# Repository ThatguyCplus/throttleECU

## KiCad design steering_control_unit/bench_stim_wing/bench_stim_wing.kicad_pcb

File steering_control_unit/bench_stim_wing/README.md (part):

# Bench stimulus FeatherWing

A FeatherWing for the EPS logger stack that does four jobs:

1. **Powers the whole stack from 12 V** (bench supply or the car battery), so the logger needs no USB power bank.
2. **Powers the Toyota steering-angle sensor** (12 V, ~30 mA, switched and fused) and passes its CAN on to the Feather M4 CAN.
3. **Drives the EPS signals** NEP (rpm) and VSP (speed) and, with the wheels off the ground, VT3/VT6 (fake driver torque).
4. **Switches IG1** for an EPS that's out of the car, on a bench.

It sits **between the Adalogger and the OLED FeatherWing**, on stacking headers, and every cable connector is right-angle and exits a board edge. The brief is [HANDOFF.md](HANDOFF.md).

> **Status: routed and checked in KiCad 10.0.8, nothing ordered.** The board is fully routed, and the Gerbers, BOM and CPL are in [fab/](fab/). Read [Before ordering](#before-ordering) first: several part numbers, the relay pinout and the JLC rotations still need a human check.
>
> | KiCad 10.0.8 check (with JLCPCB's rules, [bench_stim_wing.kicad_dru](bench_stim_wing.kicad_dru)) | Result |
> |---|---|
> | ERC | **0 errors**. 20 warnings: symbols drawn from KiCad 7's library differ from KiCad 10's copies, and KiCad 10 renamed `G6K-2` |
> | DRC | **0 copper errors, 0 unconnected, 0 schematic-parity issues**, including JLCPCB's 0.2 mm track-to-through-hole-pad rule and 1.0 mm / 0.15 mm text. Warnings left: stock footprint outlines touching their own pads (JLC clips those), footprints differ from KiCad 10's library copies, and J2's outline at the board edge (deliberate, edge connector) |

| Top (3D) | Back (3D) |
|---|---|
|  |  |

**Every part has a 3D model**, and the models ship with the project in [bench_stim_wing.3dshapes/](bench_stim_wing.3dshapes/). They're STEP files from KiCad's official library, referenced as `${KIPRJMOD}/bench_stim_wing.3dshapes/...`, so the 3D viewer and STEP export work on any machine with KiCad 7 to 10, whatever 3D libraries are installed. J1 shows the Feather stacking headers' female sockets (1×16 + 1×12). Only the test pads and the JP1 solder jumper have no model, because they're bare copper.

| Top layers | Back layers (seen from below) |
|---|---|
|  |  |

## Safety model

The user asked for this to be overbuilt. **Faking VT3/VT6 makes the EPS motor steer by itself**: front wheels off the ground (or the rack on a bench rig), hands clear of the wheel.

| Layer | What it does |
|---|---|
| **Relays, fail to the car** | Every EPS line (VT3, VT6, NEP, VSP) goes through an Omron G6K relay. The **NC** contact connects the EPS to the car's own wire, and the **NO** contact connects it to this board. No power, a reset, a crash or a blown fuse all leave the EPS wired exactly as the car wires it. |
| **ARM loop (hard kill)** | Both relay coils and the IG1 output are powered only through the **ARM loop on J5 pins 7–8**. Wire a normally-closed e-stop or a key switch there. **Loop open = car wiring, whatever the firmware does.** The red ARM LED shows the loop is closed. |
| **Enable bits** | Each output also needs its own bit from the TCA9534 I2C expander. The expander powers up with every pin as an input, and 100 kΩ pull-downs hold every driver off until firmware sets the bit. |
| **Clamped torque range** | The DAC uses its 2.048 V internal reference and the op-amp gain is 2.2, so the torque outputs top out at **4.5 V** even at full scale. They're also clamped to 0–5 V, with a 470 Ω series resistor each. |
| **Inject on the EPS side only** | NEP and VSP also feed the gauges, ECM, MCM, TCM and climate control. Only ever break them at the EPS with a breakout harness: the relay then isolates the EPS from the car wire, and the car side never sees the stimulus. |

**Latching DTCs.** The torque-sensor and sensor-supply codes (11/15/16/17/18/67) latch until erased with the SCS procedure, so a bad VT3/VT6 fake bricks assist until you clear them. The relay swaps only VT3/VT6: the real sensor stays connected to Vcc1/Vcc2 and stays powered, so the supply checks still see a real load.

**Plausibility rules** (from the manual, also in [EPS_PINOUT.md](../data_capture/EPS_PINOUT.md)):
- Never send speed without rpm. At ≥ 6.2 mph with ≤ 280 rpm for 3 s, the lamp comes on with DTC 22.
- Ramp speed changes, because VSS jumps also set DTC 22.
- Don't hold ≥ 2,000 rpm at ≤ 1 mph for more than 6 minutes.

**Key ON, engine off: the 12 V battery isn't being charged.** The DC-DC converter doesn't charge it in that state (LiBCM FAQ), so all assist current comes from the battery. Keep bench sessions short, or put a charger on the battery.

## Stack and mechanics

```
  OLED FeatherWing
  ─ female side of this wing's stacking headers ─
  BENCH STIM WING        top: relays, inductor, J2/J3/J4, LEDs   (tallest part: relays, 5.2 mm)
                         back: logic, test pads, J5              (back parts <= 1.25 mm, J5 4.25 mm)
  ─ long male tails into the Adalogger's female headers ─
  Adalogger FeatherWing  (CR1220 holder and microSD socket on its top: ~2-4 mm)
  Feather M4 CAN         (USB-C at the left end, CAN terminal block at the right end)
  EPS tap wing           (bottom wing, connectors facing down)
```

Why this slot:
- **Feather ↔ Adalogger was ruled out.** The Feather M4 CAN's 3.5 mm CAN terminal block (right end) and USB-C (left end) sit right where this board's back and its edge connectors would be.
- **The Adalogger's top is low.** The tallest parts there are the CR1220 holder (x ≈ 3–17 mm) and the microSD socket (x ≈ 27–40 mm). That's why every back-side part on this wing is ≤ 1.25 mm tall, and J5 sits at the right end, where the Adalogger is bare.
- **The OLED's underside is bare,** so the relays (5.2 mm), the inductor (3 mm) and the 4.25 mm GH connectors fit under it, inside the ~8.5 mm stacking-header gap.

Use **Feather stacking headers** (female on top, long male tails) on this wing. **Check the gap with the real parts before soldering the headers.**

### Grounding, and running with the logger

This wing and the [EPS tap wing](../data_capture/hardware/eps_tap_wing/README.md) logger run **alone or together, in the car or on a bench EPS**. [STACK_MODES.md](../data_capture/STACK_MODES.md) covers every combination: power, ground, which pins to wire, and the timers and I2C addresses they share.

**The one rule:** J2's ground (the stack's ground) goes to the **ECU end of A4 (PG, BLK)**, spliced within ~10 cm of the EPS connector. On a bench, it goes to the EPS's A4 terminal. It must not go to a chassis bolt or the battery. A4 carries the 40 A motor return, so anywhere else puts an offset between the stack and the EPS's sensor ground (B9).
- **Logger accuracy:** that offset would shift every logger reading.
- **Faked torque:** it would also shift the VT3/VT6 values this board produces.

**Leave J4.3 and J5.4 (GND) unwired in the car,** so there's only one ground path. Fitted but unpowered (J2 unplugged), this board is passive: the relays rest on the car's wiring, and the logger keeps floating on its power bank.

### Feather specification check

| Spec item | This wing |
|---|---|
| 0.9" × 2.0", 0.1" holes at each corner | 22.86 × 50.8 mm, four 2.5 mm holes 2.54 mm in from the edges |
| 16-pin and 12-pin header positions | Same footprint as the EPS tap wing; `make_pcb.py` asserts the pad positions every build |
| Power: take 3.3 V from the Feather | The expander and DAC run on the Feather's 3V3 (about 1 mA) |
| Powering the Feather from a wing | 5 V goes into the **USB pin through a Schottky** (D6). On the Feather M4 CAN the USB pin is VBUS straight off the USB-C connector, and the Feather's own MBR540 then feeds its regulator, so this is the normal path (checked against Adafruit's schematic) |
| Avoid AREF, RX/TX, SPI and its CS | AREF, RX and SPI are untouched. **TX is used** (VSP output): only D4 and RX/TX are left free in this stack, and NEP and VSP each need their own timer |
| I2C pull-ups on Wings | Not fitted: the Adalogger already has them |

### USB and 12 V at the same time

- **Our side:** the buck makes 5.05 V. After D6's drop the Feather's USB pin sees about **4.7 V**.
- **With a PC plugged in:** the PC's 5 V is higher, so the PC carries the stack and D6 stays off. This board never back-feeds the PC.
- **With 12 V gone:** D6 also stops the USB cable from powering this board's 5 V rail. The relays and op-amp go dead, and so the EPS is on the car wiring.

**A LiPo on the Feather.** If one is plugged into the Feather's JST, its charger draws up to ~200 mA from this 5 V rail. The buck is rated 0.6 A, so that still fits, but leave the LiPo off unless you want it charging.

**The current clamp's supply.** The HSTS016L on the tap wing takes its 5 V from the USB pin, so on 12 V alone it gets ~4.7 V. Its output is read as Vout − Vref, which cancels most of that offset, but **check its zero at key-on** the first time.

## Connectors

All connectors are right-angle and exit a board edge. **JLC assembles the three GH connectors** (J3, J4, J5: SMD, 1.25 mm pitch, awkward by hand). J2 (through-hole PH) and the Feather stacking headers are hand-soldered. The GH parts have locking latches: use JST GH housings (GHR-0xV-S) with SSHL-002T-P0.2 contacts, or buy pre-crimped GH leads.

**J2, 12 V IN** (top edge, JST PH S2B-PH-K, 2 mm). Pin 1 (marked +) is +12 V and pin 2 is GND. 2 A fuse.

**J3, SAS / CAN** (left end, JST GH 6-way). This is a pass-through: build one cable to the SAS, plus one pair from pins 5/6 to the Feather's CAN terminal.

| Pin | Net | Goes to |
|---|---|---|
| 1 | SAS 12V | SAS power (switched, 0.1 A PTC) |
| 2 | GND | SAS ground |
| 3 | CANH | SAS CAN-H |
| 4 | CANL | SAS CAN-L |
| 5 | CANH | Feather M4 CAN terminal **pin 3 (H)** |
| 6 | CANL | Feather M4 CAN terminal **pin 1 (L)** |

The Feather's terminal has a 120 Ω terminator behind a solder jumper (SJ2). The SAS bus here is two nodes, so close SJ2 unless the SAS end already terminates the bus.

**Second microcontroller:** J3 is also the stack's port for another board. Splice its CAN-H/CAN-L into the pin 5/6 lead (no ground or power wire), keep exactly two terminators on the bus (about 60 Ω across H/L, powered off), and use IDs 0x6C0–0x6CF. See [AUX_LINK.md](../data_capture/AUX_LINK.md).

**J4, TORQUE** (right end, top, JST GH 5-way). Break the torque sensor's VT3 and VT6 wires in a breakout harness: the CAR side goes to the sensor, the EPS side to the EPS.

| Pin | Net |
|---|---|
| 1 | VT3 EPS side (gearbox 7-pin 3 / ECU B10) |
| 2 | VT3 sensor side |
| 3 | GND (leave unwired in the car: the reference comes through J2's ground, see below) |
| 4 | VT6 EPS side (gearbox 7-pin 1 / ECU B8) |
| 5 | VT6 sensor side |

**J5, ECM / IG1 / ARM** (right end, back, JST GH 8-way). The back silk marks "J5" with pins "1" and "8"; the pin names are below.

| Pin | Net | Notes |
|---|---|---|
| 1 | IG1 OUT | Switched 12 V, 0.5 A PTC. Bench EPS only (ECU B6) |
| 2 | NEP CAR | Car-side NEP wire (ECM) |
| 3 | NEP EPS | EPS B14 |
| 4 | GND | Separates the 12 V-level pins from the 5 V-level pins. Leave unwired in the car |
| 5 | VSP EPS | EPS B4 |
| 6 | VSP CAR | Car-side VSP wire (VSS) |
| 7 | ARM+ | 5 V out to the ARM loop (0.1 A PTC) |
| 8 | ARM | Back from the loop: powers the relay coils, enables IG1 |

**Loopback for free.** The tap wing's J2 reads NEP (D6), VSP (D5), VT3 (A2) and VT6 (A3). Tap the **EPS side** of the breakout harness and the logger records exactly what the EPS receives, including whether the relay switched.

## Circuit summary

| Block | Parts | Notes |
|---|---|---|
| 12 V input | F1 2 A fast fuse → D1 SS34 (reverse polarity) → D2 SMBJ24CA TVS → C1 10 µF/50 V | Everything on +12 V is rated ≥ 40 V; the TVS clamps a load dump to ~39 V |
| 5 V | U1 LMR16006 (40 V, 65 V transient, 0.6 A, 0.7 MHz), L1 22 µH, D4 catch diode, 56k/10k → 5.05 V | ~250 mA load: stack ~150 mA, relays 2 × 28 mA, LEDs |
| Feather feed | D6 PMEG6010 → Feather USB pin | See [USB and 12 V at the same time](#usb-and-12-v-at-the-same-time) |
| SAS power | Q1 Si2319 high side, Q2 2N7002, F2 0.1 A PTC | Expander P0. **JP1** (open as shipped): bridge for "SAS always on", for use with the unmodified logger firmware |
| IG1 out | Q3 Si2319, Q4 + Q5 in series (IG1_EN **and** ARM), F4 0.5 A PTC | Expander P1 |
| Relays | K1 (VT3/VT6), K2 (NEP/VSP): G6K-2F-Y 5 V, Q6/Q7 drivers, 1N4148WS flyback | Expander P2, P3. Coils fed from ARM |
| NEP | D4 (PA14) → Q8 → open drain, **4.7 kΩ to 12 V**, 100 Ω series | Like the ECM's open-collector output |
| VSP | TX (PB16) → Q9 → open drain, **4.7 kΩ to 5 V**, 100 Ω series | Like the VSS |
| Torque | U2 MCP4728 (I2C 0x60, 2.048 V ref, gain ×1) → U3 MCP6004 on 5 V, gain 2.2 → 470 Ω → BAT54S clamp | DAC A = VT3, B = VT6. DAC C and D go **straight** to test pads 10/11 as spare 0–2.048 V outputs (unbuffered, ~mA); op-amp sections C/D are parked as grounded followers |
| Expander | U4 TCA9534 (I2C **0x20**) | P0 SAS, P1 IG1, P2 K1, P3 K2 (outputs); P4 ARM sense, P5 12 V sense (inputs); P6/P7 on test pads |

**Pulse output polarity.** GPIO high pulls the output low (open drain), and the idle level is high. Both D4 and TX sit on independent timers: PA14 on TCC1/WO2 or TCC2/WO0, PB16 on TC6/WO0 or TCC0/WO4. **Don't use TC3**: the logger (`eps_logger`) uses it for its 1 kHz sample tick. The rates are low (NEP 1.5 pulses/rev: 22.5 Hz at 900 rpm; VSP ~1.24 Hz per mph, **unverified**), so plain `micros()` timing also works.

**I2C addresses** on the shared bus: RTC 0x68, OLED 0x3C, ADS1115 0x48, **MCP4728 0x60, TCA9534 0x20**. There are no clashes.

### LEDs

Top side, in one row above the relays. Left to right: **5V, SAS, IG1, ARM, TQ, SIG, NEP, VSP**; the legend is also on the back silk. The 12 V LED is in the top-left corner. TQ and SIG light when their relay is energised. NEP and VSP blink with the pulse outputs.

### Test pads (back)

The pads are numbered 1–15 on the back silk; names don't fit at JLC's 1 mm minimum text height.

| TP | Net | TP | Net | TP | Net |
|---|---|---|---|---|---|
| 1 | GND | 6 | NEP out | 11 | DAC D (raw, 0–2.048 V) |
| 2 | +12 V | 7 | VSP out | 12 | ARM |
| 3 | +5 V | 8 | VT3 out | 13 | Expander P6 |
| 4 | +3V3 | 9 | VT6 out | 14 | Expander P7 |
| 5 | USB pin | 10 | DAC C (raw, 0–2.048 V) | 15 | GND |

## Design rules

| Item | Value |
|---|---|
| Layers | 4: **F.Cu** parts + signals + GND pour, **In1.Cu** solid GND, **In2.Cu** signals + GND pour, **B.Cu** parts + signals + GND pour |
| Signal tracks | 0.15 mm (mA and below) |
| Power tracks | +12 V path and IG1 0.5 mm; +5 V, USB, buck SW, SAS and ARM 0.4 mm; 3V3 0.3 mm |
| Clearance | 0.127 mm; **0.21 mm from tracks to plated through-hole pads** (JLCPCB's 0.2 mm pad-to-trace rule) |
| GND plane | In1 is a solid GND pour; a few low-speed signals cross it where routing needed the room |
| Silkscreen | All text >= 1.0 mm high with a 0.15 mm stroke (JLCPCB minimum) |
| JLCPCB rules | [bench_stim_wing.kicad_dru](bench_stim_wing.kicad_dru), the 4-layer 1 oz set from [Cimos/kicad-druid](https://github.com/Cimos/kicad-druid) (MIT). KiCad loads it as the project's custom rules |
| Vias | 0.45/0.2 mm signal, 0.6/0.3 mm power |
| Assembly | **Both sides** (SMD top and back). The back carries only parts ≤ 1.25 mm tall |

## Files

| File | What it is |
|---|---|
| [bench_stim_wing.kicad_sch](bench_stim_wing.kicad_sch) / [schematic PDF](doc/bench_stim_wing_schematic.pdf) | Schematic (generated) |
| [bench_stim_wing.kicad_pcb](bench_stim_wing.kicad_pcb) | Board, 50.8 × 22.86 mm (FeatherWing), 4 layers |
| [doc/](doc/) | 3D renders (KiCad 10) and layer renders of the top and back |
| [bench_stim_wing.3dshapes/](bench_stim_wing.3dshapes/) | The 3D models every footprint points to (KiCad library STEP files, CC-BY-SA 4.0 with the KiCad library exception) |
| [fab/](fab/) | Gerbers + drill (zipped), JLC BOM and CPL. All SMD parts including the GH connectors; J1 (stacking headers), J2, JP1 and the test pads are excluded |
| [gen/](gen/) | Generators. Everything comes from [gen/design.py](gen/design.py) (parts and nets) and [gen/placement.py](gen/placement.py) (positions, silk, hand stubs). [gen/bench_stim_wing.ses](gen/bench_stim_wing.ses) is the accepted Freerouting result |

## Rebuilding

The board was generated in a Linux cloud session. The generators ran on **KiCad 7.0.11**, the version Ubuntu ships. Sign-off ran on **KiCad 10.0.8**, which [gen/setup_kicad10.sh](gen/setup_kicad10.sh) installs from the official `kicad/kicad` Docker image. That image comes through Google's Docker Hub mirror, because KiCad's Launchpad PPA is blocked there and Docker Hub rate-limits anonymous pulls. The script runs KiCad 10 through `chroot`, which needs root. Routing used **Freerouting 1.9.0** on Java 21, under `xvfb-run`. The files are written in KiCad 7's format. KiCad 10 opens them and asks to upgrade on save. Upgrading is fine, but then the generators would overwrite your edits, so pick one way of working.

```bash
cd gen
sh route.sh --keep-routing   # rebuild everything from the committed routing (bench_stim_wing.ses)
sh route.sh                  # full re-route with Freerouting (a different result every run)
```

`route.sh` expects `kicad-cli` and a Python that can `import pcbnew` (`PY=...`). A full re-route also needs the Freerouting 1.9 jar (`JAR=...`). On Windows with KiCad 10, point `PY` at KiCad's bundled `python.exe`, and set `KICAD_SYMBOL_DIR` / `KICAD_FOOTPRINT_DIR` if the libraries aren't found.

**How it got to 0 unconnected (and JLCPCB-clean):**
- **Freerouting version.** 2.0.1 ignored its pass limit and never finished, so routing uses 1.9.0 with `-oit 100`. Without that flag the post-route optimiser runs for hours.
- **Rules.** Signal tracks are 0.15 mm with 0.127 mm clearance, but tracks stay **0.21 mm from plated through-hole pads**, per JLCPCB's 0.2 mm pad-to-trace rule. KiCad 7 doesn't export per-pad clearances to Freerouting, so `make_pcb.py` grows the through-hole pads in the router's copy of the board instead (`dsn_router_tweaks`).
- **Spare DAC channels simplified.** DAC C/D used to have their own op-amp stages. Routing those with the wider through-hole clearance left nets unroutable, so they now go straight to test pads 10/11.
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
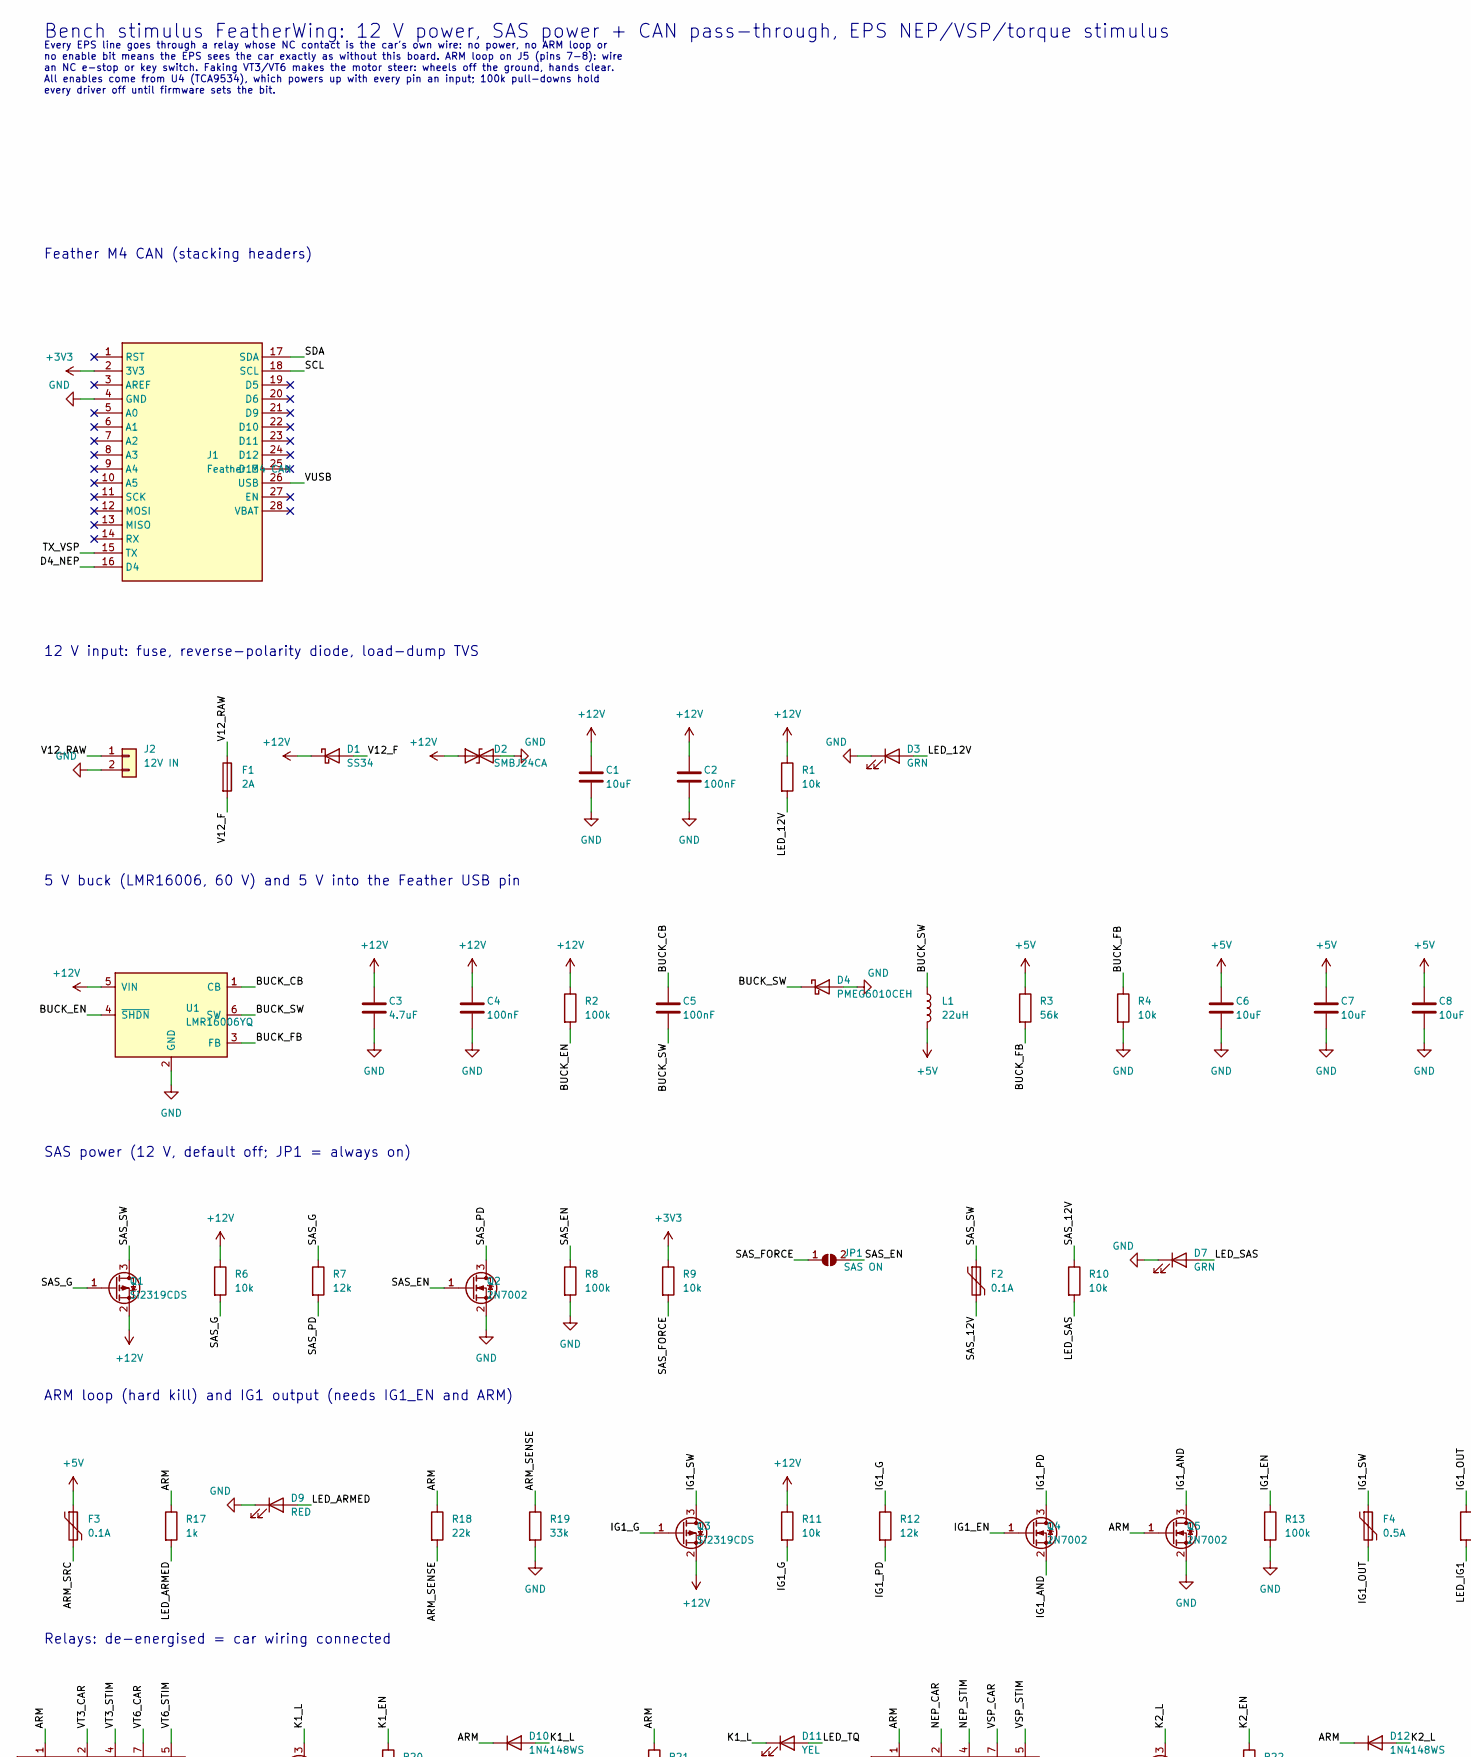
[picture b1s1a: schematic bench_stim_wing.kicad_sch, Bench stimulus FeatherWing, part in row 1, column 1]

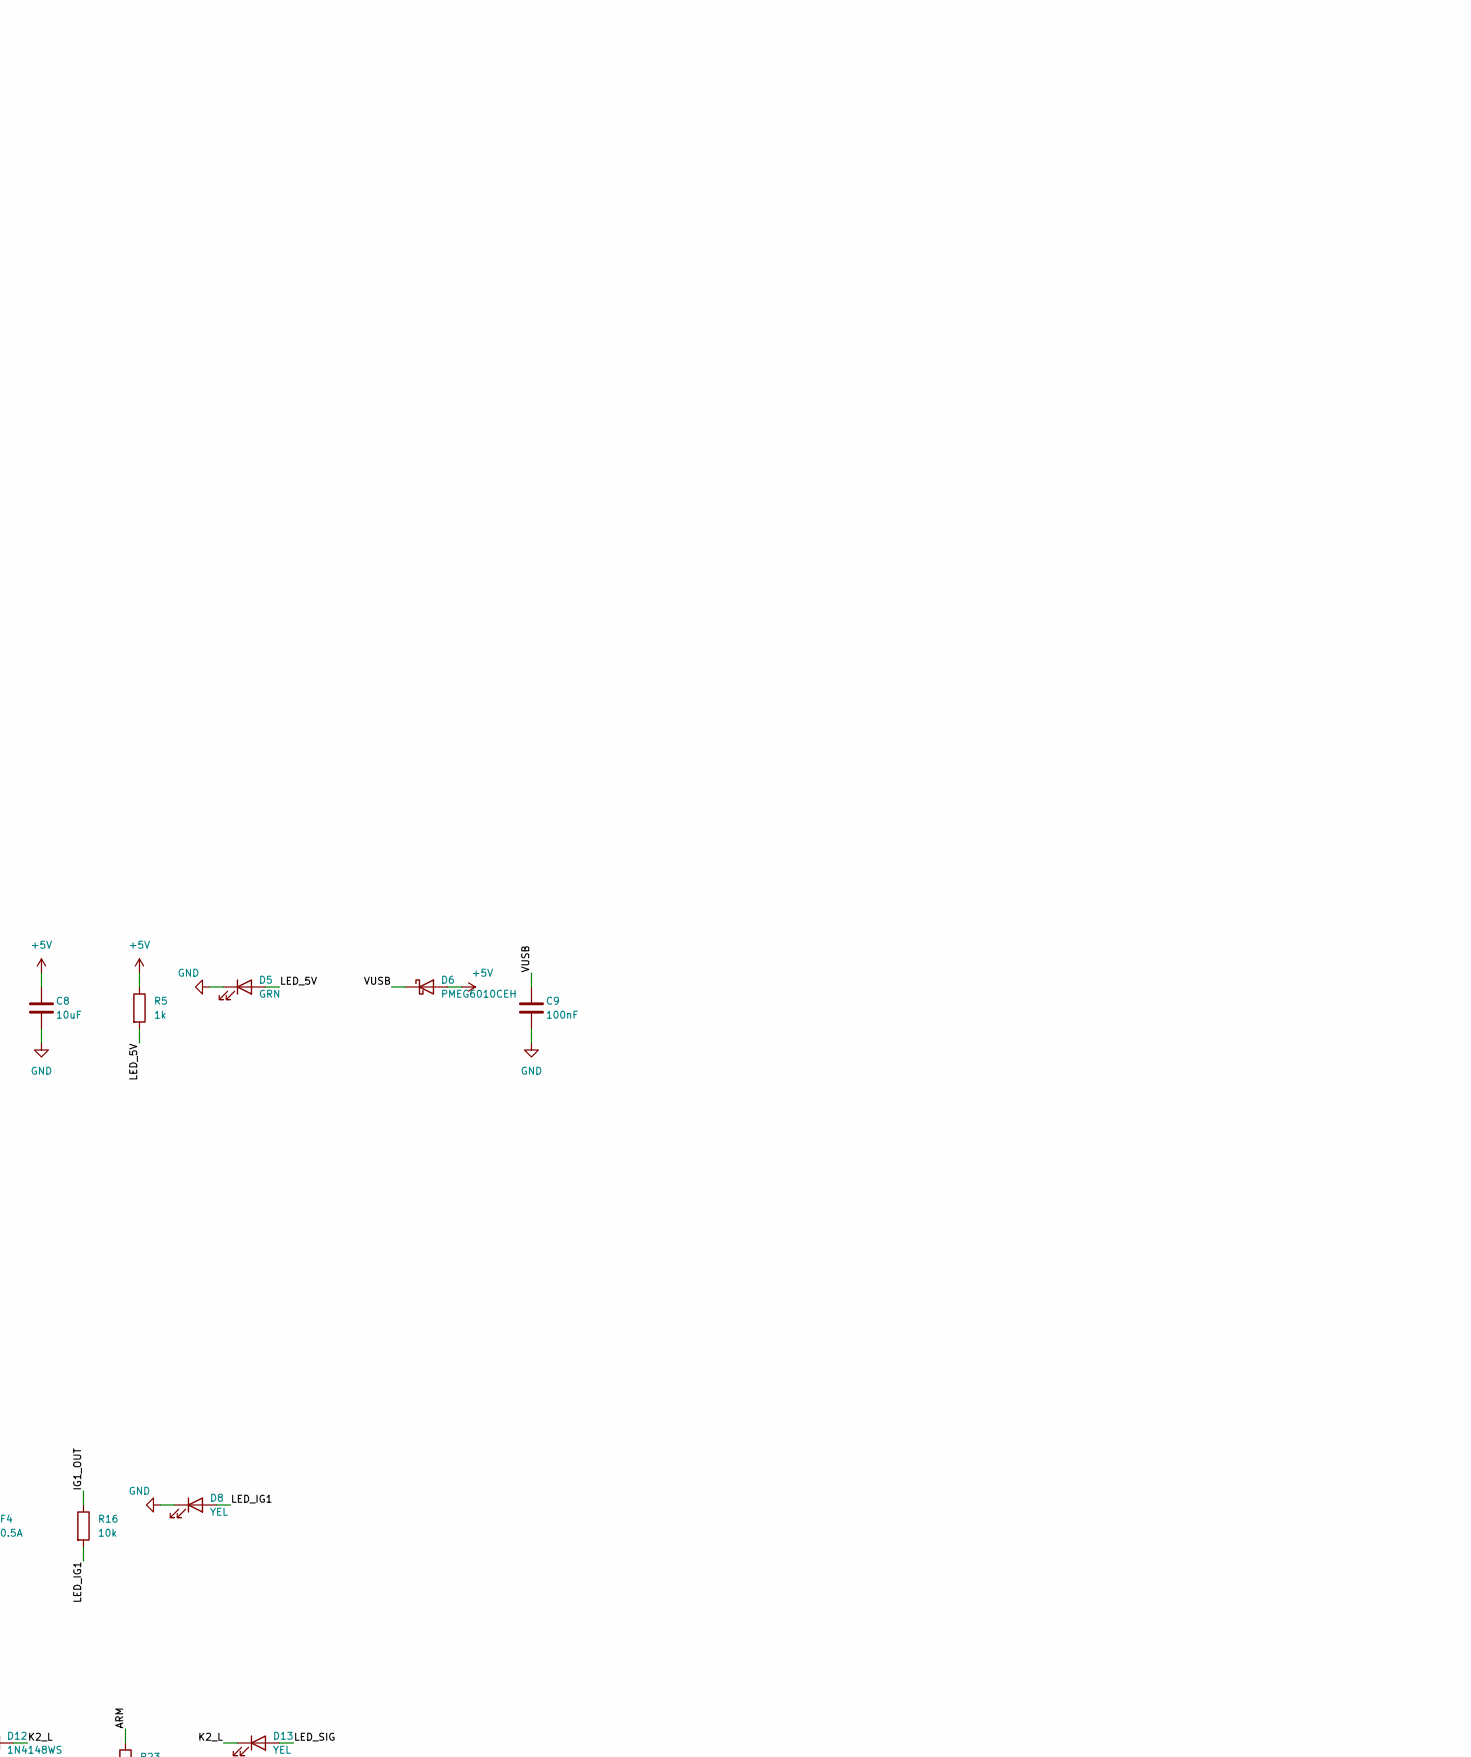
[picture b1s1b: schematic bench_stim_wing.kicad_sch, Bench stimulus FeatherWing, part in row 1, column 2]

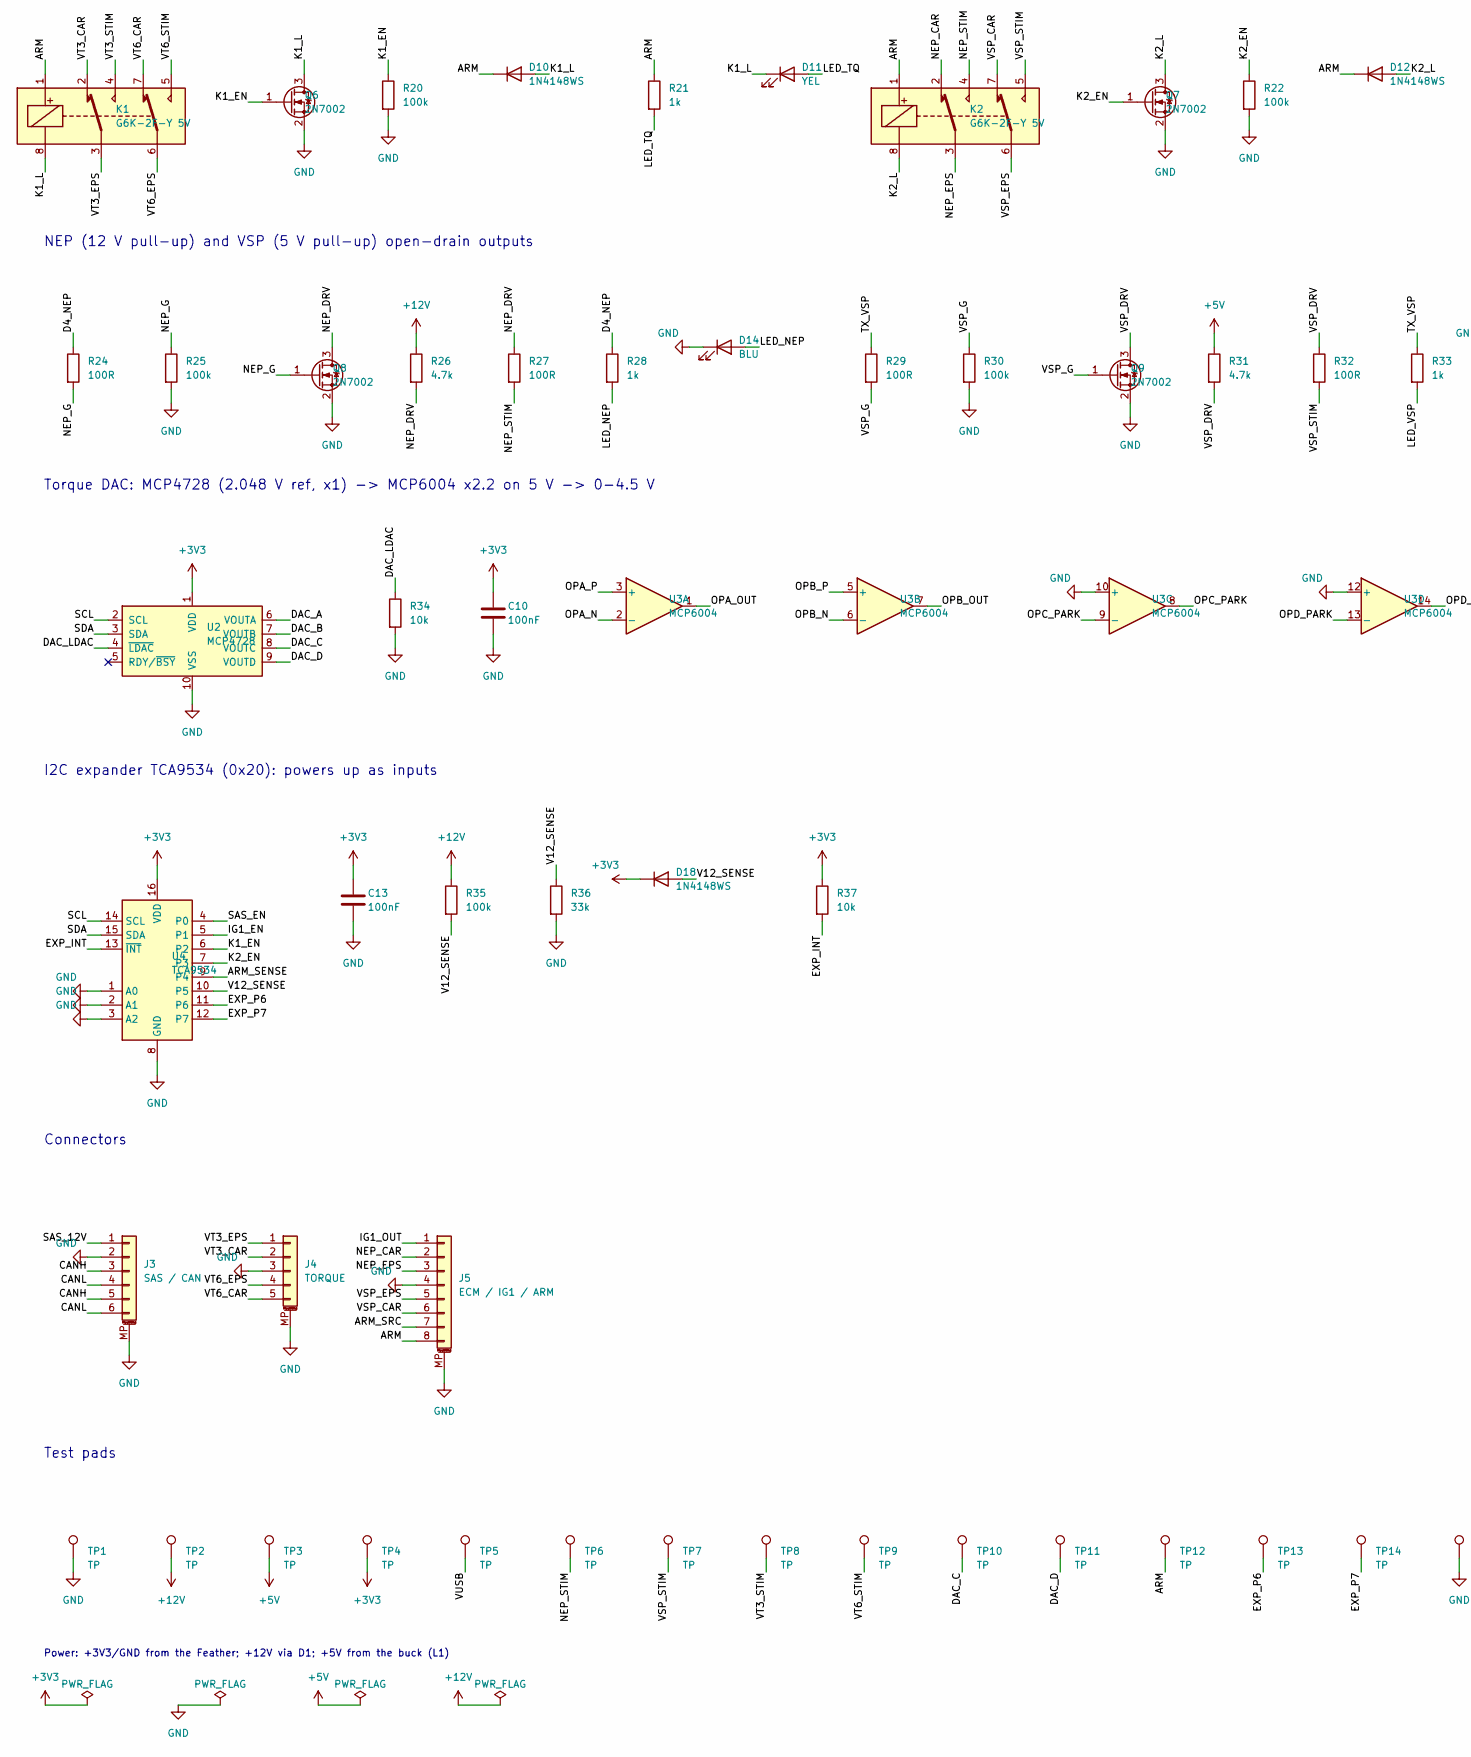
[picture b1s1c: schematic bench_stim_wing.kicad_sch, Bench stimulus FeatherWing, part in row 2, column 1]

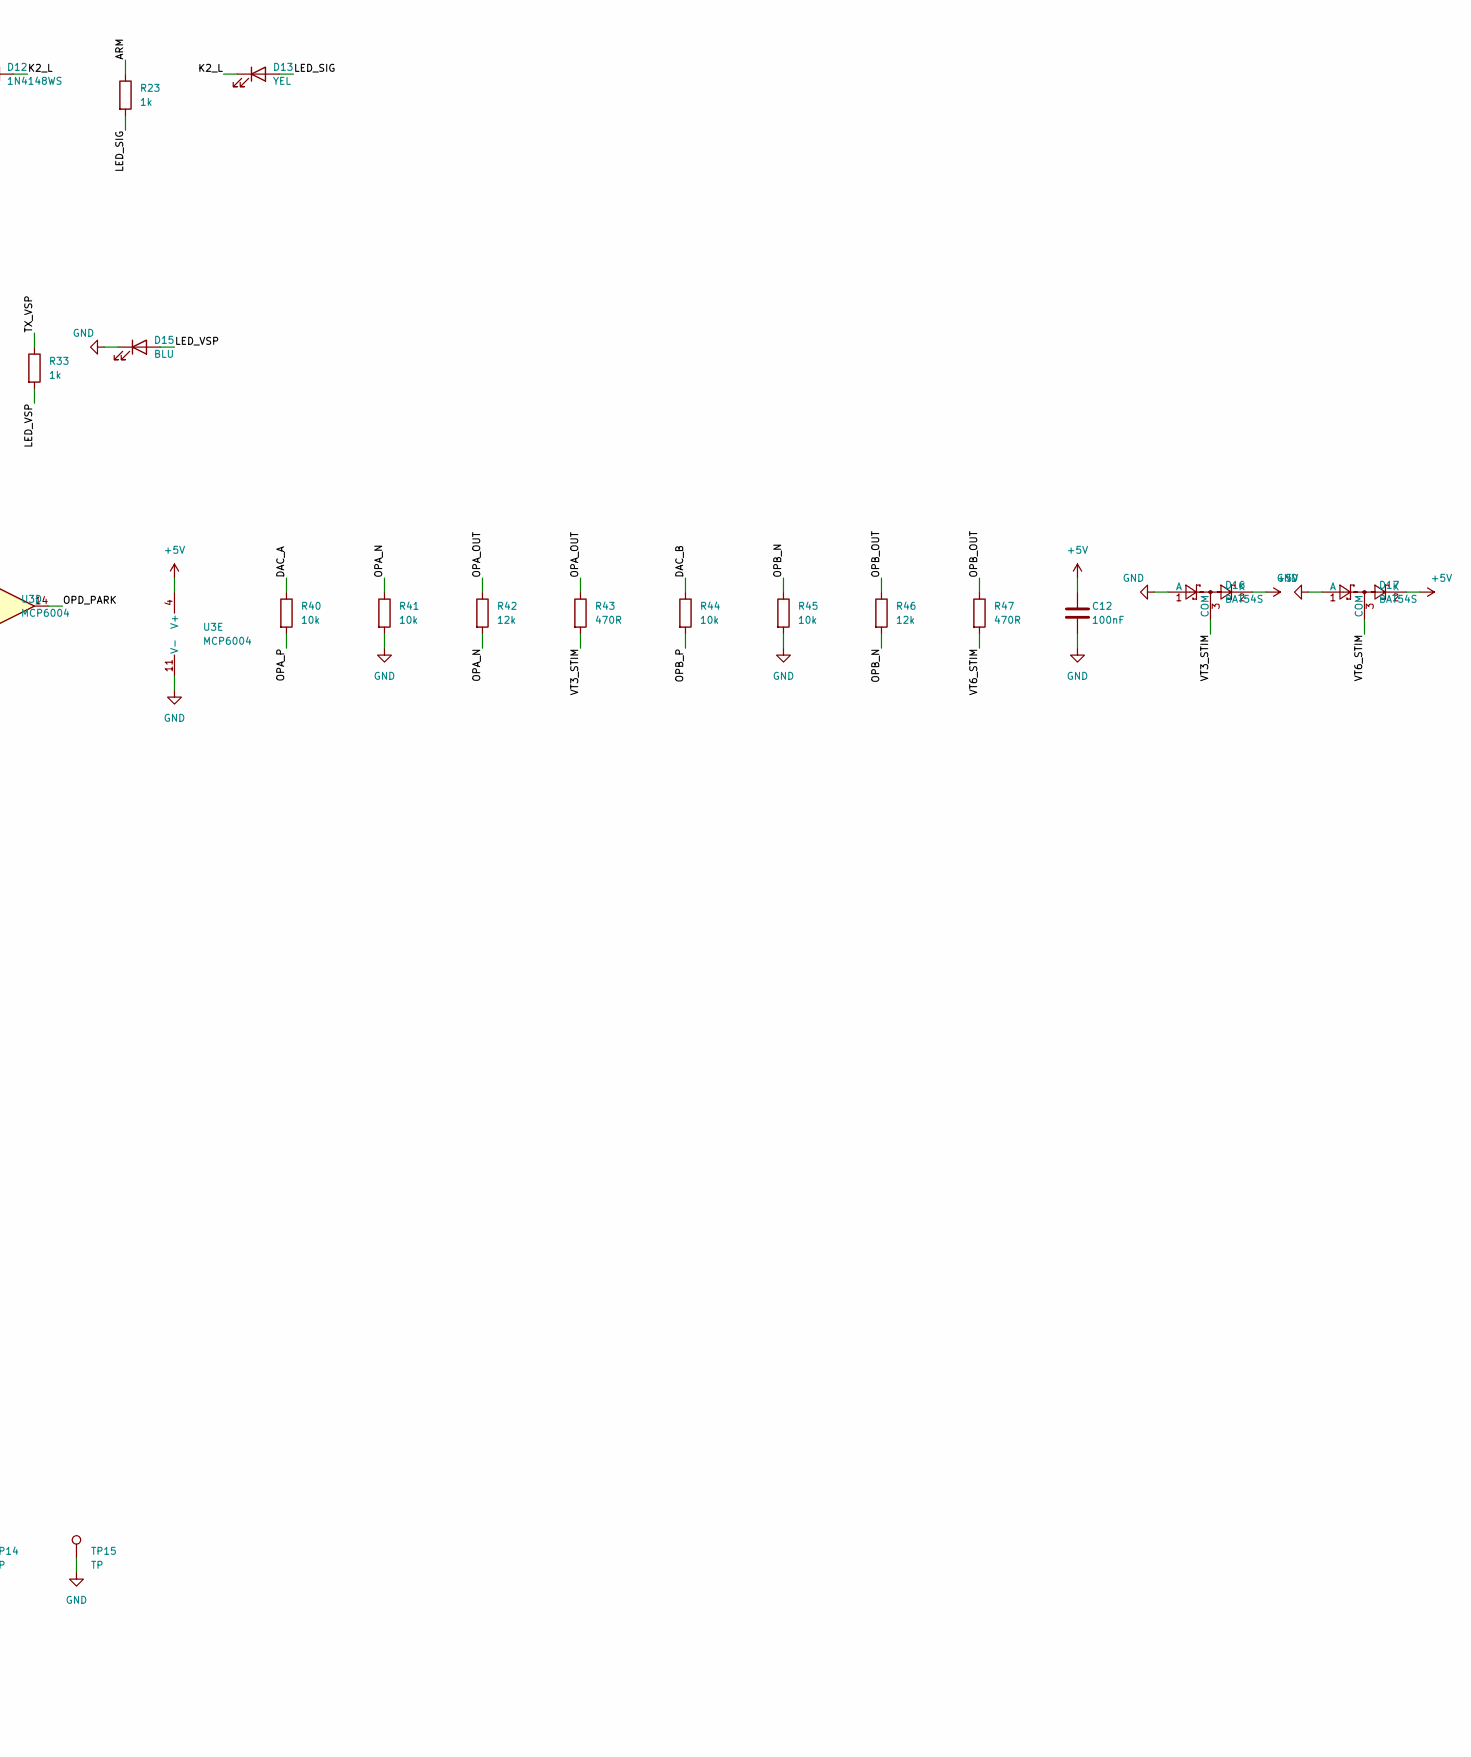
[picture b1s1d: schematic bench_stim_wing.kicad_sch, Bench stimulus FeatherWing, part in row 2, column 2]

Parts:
C1: 10uF; C_1206_3216Metric; MPN CL31A106KBHNNNE; LCSC C13585
C2, C4: 100nF; C_0603_1608Metric; MPN CC0603KRX7R9BB104; LCSC C14663
C3: 4.7uF; C_1206_3216Metric; MPN CL31B475KBHNNNE; LCSC C51205
C5, C9, C10, C12, C13: 100nF; C_0402_1005Metric; MPN CL05B104KO5NNNC; LCSC C1525
C6, C7, C8: 10uF; C_0805_2012Metric; MPN CL21A106KAYNNNE; LCSC C15850
D1: SS34; D_SMA; MPN SS34; LCSC C8678
D2: SMBJ24CA; D_SMB; MPN SMBJ24CA (Bourns); LCSC C1973089
D3, D5, D7: GRN; LED_0603_1608Metric; MPN KT-0603G; LCSC C12624
D4, D6: PMEG6010CEH; D_SOD-123F; MPN PMEG6010CEH-QX; LCSC C5311567
D8, D11, D13: YEL; LED_0603_1608Metric; MPN KT-0603Y; LCSC C2287
D9: RED; LED_0603_1608Metric; MPN KT-0603R; LCSC C2286
D10, D12, D18: 1N4148WS; D_SOD-323; MPN 1N4148WS; LCSC C2128
D14, D15: BLU; LED_0603_1608Metric; MPN KT-0603B; LCSC C2288
D16, D17: BAT54S; SOT-23; MPN BAT54S; LCSC C171786
F1: 2A; Fuse_1206_3216Metric; MPN 0466002.NRHF; LCSC C3105
F2, F3: 0.1A; Fuse_1206_3216Metric; MPN 1206L010/60WR; LCSC C2153714
F4: 0.5A; Fuse_1206_3216Metric; MPN 1206L050/30NR (LUTE); LCSC C7542947
J1: Feather M4 CAN; Feather_Wing_Headers
J2: 12V IN; JST_PH_S2B-PH-K_1x02_P2.00mm_Horizontal
J3: SAS / CAN; JST_GH_SM06B-GHS-TB_1x06-1MP_P1.25mm_Horizontal; MPN SM06B-GHS-TB(LF)(SN); LCSC C133065
J4: TORQUE; JST_GH_SM05B-GHS-TB_1x05-1MP_P1.25mm_Horizontal; MPN SM05B-GHS-TB(LF)(SN); LCSC C189896
J5: ECM / IG1 / ARM; JST_GH_SM08B-GHS-TB_1x08-1MP_P1.25mm_Horizontal; MPN SM08B-GHS-TB(LF)(SN); LCSC C265111
JP1: SAS ON; SolderJumper_Plain
K1, K2: G6K-2F-Y 5V; Relay_DPDT_Omron_G6K-2F-Y; MPN G6K-2F-Y DC5; LCSC C231389
L1: 22uH; L_Cenker_CKCS4030; MPN SWPA4030S220MT; LCSC C83472
Q1, Q3: Si2319CDS; SOT-23; MPN SI2319CDS-T1-GE3; LCSC C146287
Q2, Q4, Q5, Q6, Q7, Q8, Q9: 2N7002; SOT-23; MPN 2N7002; LCSC C8545
R1, R4, R6, R9, R10, R11, R16, R34, R37, R40, R41, R44, R45: 10k; R_0402_1005Metric; MPN 0402WGF1002TCE; LCSC C25744
R2, R8, R13, R20, R22, R25, R30, R35: 100k; R_0402_1005Metric; MPN 0402WGF1003TCE; LCSC C25741
R3: 56k; R_0402_1005Metric; MPN 0402WGF5602TCE; LCSC C25796
R5, R17, R21, R23, R28, R33: 1k; R_0402_1005Metric; MPN 0402WGF1001TCE; LCSC C11702
R7, R12, R42, R46: 12k; R_0402_1005Metric; MPN 0402WGF1202TCE; LCSC C25752
R18: 22k; R_0402_1005Metric; MPN 0402WGF2202TCE; LCSC C25768
R19, R36: 33k; R_0402_1005Metric; MPN 0402WGF3302TCE; LCSC C25779
R24, R27, R29, R32: 100R; R_0402_1005Metric; MPN 0402WGF1000TCE; LCSC C25076
R26, R31: 4.7k; R_0603_1608Metric; MPN 0603WAF4701T5E; LCSC C23162
R43, R47: 470R; R_0402_1005Metric; MPN 0402WGF4700TCE; LCSC C25117
TP1, TP2, TP3, TP4, TP5, TP6, TP7, TP8, TP9, TP10, TP11, TP12, TP13, TP14, TP15: TP; TestPoint_Pad_D1.0mm
U1: LMR16006YQ; SOT-23-6; MPN LMR16006YQDDCRQ1; LCSC C544521
U2: MCP4728; MSOP-10_3x3mm_P0.5mm; MPN MCP4728-E/UN; LCSC C108207
U3: MCP6004; TSSOP-14_4.4x5mm_P0.65mm; MPN MCP6004T-I/ST; LCSC C50282
U4: TCA9534; TSSOP-16_4.4x5mm_P0.65mm; MPN TCA9534PWR; LCSC C783615

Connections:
+3V3: C10.1, C13.1, D18.1 (K), J1.2 (3V3), R9.1, R37.1, TP4.1, U2.1 (VDD), U4.16 (VDD)
+5V: C6.1, C7.1, C8.1, C12.1, D6.2 (A), D16.2 (K), D17.2 (K), F3.1, L1.2, R3.1, R5.1, R31.1, TP3.1, U3.4 (V+)
+12V: C1.1, C2.1, C3.1, C4.1, D1.1 (K), D2.1 (A1), Q1.2 (S), Q3.2 (S), R1.1, R2.1, R6.1, R11.1, R26.1, R35.1, TP2.1, U1.5 (VIN)
/ARM: D10.1 (K), D12.1 (K), J5.8, K1.1, K2.1, Q5.1 (G), R17.1, R18.1, R21.1, R23.1, TP12.1
/ARM_SENSE: R18.2, R19.1, U4.9 (P4)
/ARM_SRC: F3.2, J5.7
/BUCK_CB: C5.1, U1.1 (CB)
/BUCK_EN: R2.2, U1.4 (~SHDN)
/BUCK_FB: R3.2, R4.1, U1.3 (FB)
/BUCK_SW: C5.2, D4.1 (K), L1.1, U1.6 (SW)
/CANH: J3.3, J3.5
/CANL: J3.4, J3.6
/D4_NEP: J1.16 (D4), R24.1, R28.1
/DAC_A: R40.1, U2.6 (VOUTA)
/DAC_B: R44.1, U2.7 (VOUTB)
/DAC_C: TP10.1, U2.8 (VOUTC)
/DAC_D: TP11.1, U2.9 (VOUTD)
/DAC_LDAC: R34.1, U2.4 (~LDAC)
/EXP_INT: R37.2, U4.13 (~INT)
/EXP_P6: TP13.1, U4.11 (P6)
/EXP_P7: TP14.1, U4.12 (P7)
/IG1_AND: Q4.2 (S), Q5.3 (D)
/IG1_EN: Q4.1 (G), R13.1, U4.5 (P1)
/IG1_G: Q3.1 (G), R11.2, R12.1
/IG1_OUT: F4.2, J5.1, R16.1
/IG1_PD: Q4.3 (D), R12.2
/IG1_SW: F4.1, Q3.3 (D)
/K1_EN: Q6.1 (G), R20.1, U4.6 (P2)
/K1_L: D10.2 (A), D11.1 (K), K1.8, Q6.3 (D)
/K2_EN: Q7.1 (G), R22.1, U4.7 (P3)
/K2_L: D12.2 (A), D13.1 (K), K2.8, Q7.3 (D)
/LED_5V: D5.2 (A), R5.2
/LED_12V: D3.2 (A), R1.2
/LED_ARMED: D9.2 (A), R17.2
/LED_IG1: D8.2 (A), R16.2
/LED_NEP: D14.2 (A), R28.2
/LED_SAS: D7.2 (A), R10.2
/LED_SIG: D13.2 (A), R23.2
/LED_TQ: D11.2 (A), R21.2
/LED_VSP: D15.2 (A), R33.2
/NEP_CAR: J5.2, K2.2
/NEP_DRV: Q8.3 (D), R26.2, R27.1
/NEP_EPS: J5.3, K2.3
/NEP_G: Q8.1 (G), R24.2, R25.1
/NEP_STIM: K2.4, R27.2, TP6.1
/OPA_N: R41.1, R42.2, U3.2 (-)
/OPA_OUT: R42.1, R43.1, U3.1
/OPA_P: R40.2, U3.3 (+)
/OPB_N: R45.1, R46.2, U3.6 (-)
/OPB_OUT: R46.1, R47.1, U3.7
/OPB_P: R44.2, U3.5 (+)
/OPC_PARK: U3.8, U3.9 (-)
/OPD_PARK: U3.13 (-), U3.14
/SAS_12V: F2.2, J3.1, R10.1
/SAS_EN: JP1.2 (B), Q2.1 (G), R8.1, U4.4 (P0)
/SAS_FORCE: JP1.1 (A), R9.2
/SAS_G: Q1.1 (G), R6.2, R7.1
/SAS_PD: Q2.3 (D), R7.2
/SAS_SW: F2.1, Q1.3 (D)
/SCL: J1.18 (SCL), U2.2 (SCL), U4.14 (SCL)
/SDA: J1.17 (SDA), U2.3 (SDA), U4.15 (SDA)
/TX_VSP: J1.15 (TX), R29.1, R33.1
/V12_F: D1.2 (A), F1.2
/V12_RAW: F1.1, J2.1
/V12_SENSE: D18.2 (A), R35.2, R36.1, U4.10 (P5)
/VSP_CAR: J5.6, K2.7
/VSP_DRV: Q9.3 (D), R31.2, R32.1
/VSP_EPS: J5.5, K2.6
/VSP_G: Q9.1 (G), R29.2, R30.1
/VSP_STIM: K2.5, R32.2, TP7.1
/VT3_CAR: J4.2, K1.2
/VT3_EPS: J4.1, K1.3
/VT3_STIM: D16.3 (COM), K1.4, R43.2, TP8.1
/VT6_CAR: J4.5, K1.7
/VT6_EPS: J4.4, K1.6
/VT6_STIM: D17.3 (COM), K1.5, R47.2, TP9.1
/VUSB: C9.1, D6.1 (K), J1.26 (USB), TP5.1
GND: C1.2, C2.2, C3.2, C4.2, C6.2, C7.2, C8.2, C9.2, C10.2, C12.2, C13.2, D2.2 (A2), D3.1 (K), D4.2 (A), D5.1 (K), D7.1 (K), D8.1 (K), D9.1 (K), D14.1 (K), D15.1 (K), D16.1 (A), D17.1 (A), J1.4 (GND), J2.2, J3.2, J3.MP (MountPin), J4.3, J4.MP (MountPin), J5.4, J5.MP (MountPin), Q2.2 (S), Q5.2 (S), Q6.2 (S), Q7.2 (S), Q8.2 (S), Q9.2 (S), R4.2, R8.2, R13.2, R19.2, R20.2, R22.2, R25.2, R30.2, R34.2, R36.2, R41.2, R45.2, TP1.1, TP15.1, U1.2 (GND), U2.10 (VSS), U3.10 (+), U3.11 (V-), U3.12 (+), U4.1 (A0), U4.2 (A1), U4.3 (A2), U4.8 (GND)

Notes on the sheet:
Bench stimulus FeatherWing: 12 V power, SAS power + CAN pass-through, EPS NEP/VSP/torque stimulus
Every EPS line goes through a relay whose NC contact is the car's own wire: no power, no ARM loop or no enable bit means the EPS sees the car exactly as without this board. ARM loop on J5 (pins 7-8): wire an NC e-stop or key switch. Faking VT3/VT6 makes the motor steer: wheels off the ground, hands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
Feather M4 CAN (stacking headers)
12 V input: fuse, reverse-polarity diode, load-dump TVS
5 V buck (LMR16006, 60 V) and 5 V into the Feather USB pin
SAS power (12 V, default off; JP1 = always on)
ARM loop (hard kill) and IG1 output (needs IG1_EN and ARM)
Relays: de-energised = car wiring connected
NEP (12 V pull-up) and VSP (5 V pull-up) open-drain outputs
Torque DAC: MCP4728 (2.048 V ref, x1) -> MCP6004 x2.2 on 5 V -> 0-4.5 V
I2C expander TCA9534 (0x20): powers up as inputs
Connectors
Test pads
Power: +3V3/GND from the Feather; +12V via D1; +5V from the buck (L1)

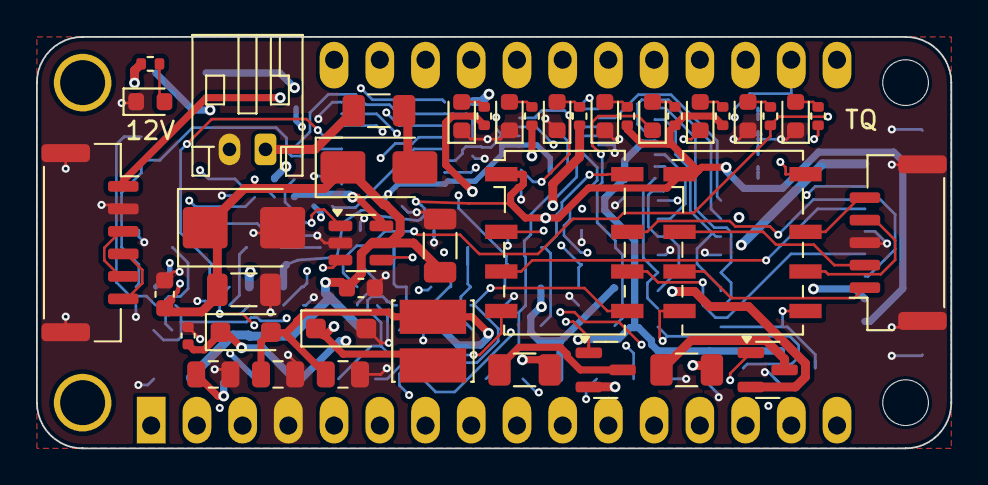
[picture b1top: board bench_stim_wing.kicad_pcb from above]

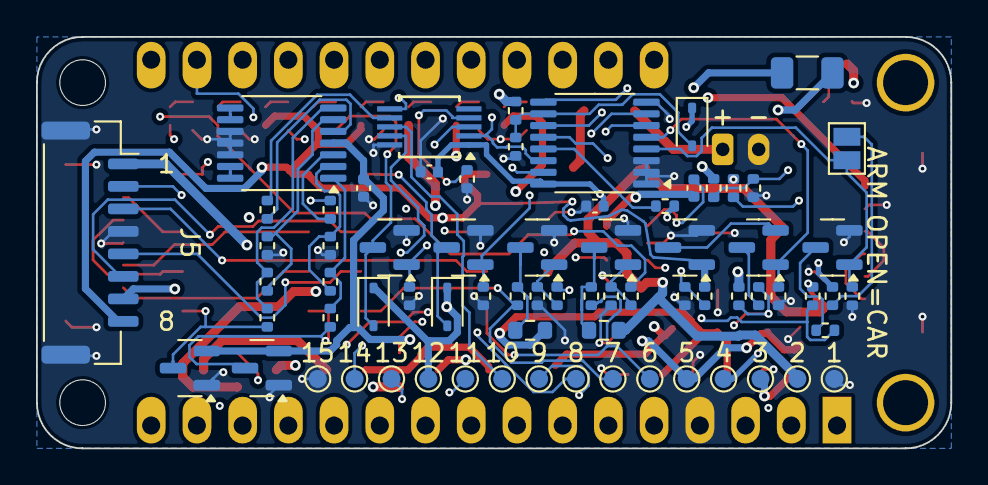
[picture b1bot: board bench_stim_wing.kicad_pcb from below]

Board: 4 copper layers, 50.8 x 22.9 mm, 114 parts (71 on the bottom side), 78 nets.

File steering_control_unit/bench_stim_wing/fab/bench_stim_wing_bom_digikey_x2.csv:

Customer Reference,Manufacturer,Manufacturer Part Number,Quantity,Per board,Description
C1,Samsung Electro-Mechanics,CL31A106KBHNNNE,10,1,10uF 50V X5R 1206
"C2,C4",YAGEO,CC0603KRX7R9BB104,10,2,100nF 50V X7R 0603
C3,Samsung Electro-Mechanics,CL31B475KBHNNNE,10,1,4.7uF 50V X7R 1206
"C5,C9,C10,C12,C13",Samsung Electro-Mechanics,CL05B104KO5NNNC,20,5,100nF 16V X7R 0402
"C6,C7,C8",Samsung Electro-Mechanics,CL21A106KAYNNNE,10,3,10uF 25V X5R 0805
D1,Vishay General Semiconductor,SS34-E3/57T,4,1,Schottky 40V 3A SMA (DO-214AC)
D2,Bourns,SMBJ24CA,4,1,TVS 24V bidirectional 600W SMB
"D3,D5,D7",Lite-On,LTST-C191KGKT,10,3,LED green 0603
"D4,D6",Nexperia,PMEG6010CEH-QX,6,2,"Schottky 60V 1A SOD-123F (alt: PMEG6010CEH,115)"
"D8,D11,D13",Lite-On,LTST-C191KSKT,10,3,LED yellow 0603
D9,Lite-On,LTST-C191KRKT,10,1,LED red 0603
"D10,D12,D18",Diodes Incorporated,1N4148WS-7-F,10,3,Switching diode 100V SOD-323
"D14,D15",Lite-On,LTST-C191TBKT,10,2,LED blue 0603
"D16,D17",Nexperia,"BAT54S,215",6,2,Dual Schottky series SOT-23
F1,Littelfuse,0466002.NR,4,1,Fuse 2A 63V very fast 1206
"F2,F3",Littelfuse,1206L010/60WR,6,2,PTC 0.1A hold 60V 1206
F4,Littelfuse,1206L050/24WR,4,1,PTC 0.5A hold 24V 1206 (JLC build used a 30V part; none at DigiKey)
J3,JST,SM06B-GHS-TB(LF)(SN),3,1,GH 6-pin right-angle SMD header
J4,JST,SM05B-GHS-TB(LF)(SN),3,1,GH 5-pin right-angle SMD header
J5,JST,SM08B-GHS-TB(LF)(SN),3,1,GH 8-pin right-angle SMD header
"K1,K2",Omron Electronics,G6K-2F-Y DC5,4,2,Relay DPDT 5V SMD
L1,Bourns,SRN4026-220M,3,1,22uH shielded 4x4 mm (replaces Sunlord SWPA4030S220MT)
"Q1,Q3",Vishay Siliconix,SI2319CDS-T1-GE3,6,2,P-MOSFET -40V SOT-23
"Q2,Q4,Q5,Q6,Q7,Q8,Q9",onsemi,2N7002LT1G,20,7,N-MOSFET 60V SOT-23
"R1,R4,R6,R9,R10,R11,R16,R34,R37,R40,R41,R44,R45",YAGEO,RC0402FR-0710KL,50,13,10k 1% 0402
"R2,R8,R13,R20,R22,R25,R30,R35",YAGEO,RC0402FR-07100KL,25,8,100k 1% 0402
R3,YAGEO,RC0402FR-0756KL,10,1,56k 1% 0402
"R5,R17,R21,R23,R28,R33",YAGEO,RC0402FR-071KL,25,6,1k 1% 0402
"R7,R12,R42,R46",YAGEO,RC0402FR-0712KL,10,4,12k 1% 0402
R18,YAGEO,RC0402FR-0722KL,10,1,22k 1% 0402
"R19,R36",YAGEO,RC0402FR-0733KL,10,2,33k 1% 0402
"R24,R27,R29,R32",YAGEO,RC0402FR-07100RL,10,4,100R 1% 0402
"R26,R31",YAGEO,RC0603FR-074K7L,10,2,4.7k 1% 0603
"R43,R47",YAGEO,RC0402FR-07470RL,10,2,470R 1% 0402
U1,Texas Instruments,LMR16006YQDDCRQ1,3,1,Buck 40V 0.6A SOT-23-6
U2,Microchip Technology,MCP4728-E/UN,3,1,Quad 12-bit DAC I2C MSOP-10
U3,Microchip Technology,MCP6004T-I/ST,3,1,Quad op-amp TSSOP-14
U4,Texas Instruments,TCA9534PWR,3,1,I2C 8-bit expander TSSOP-16
J1,Adafruit Industries LLC,2830,2,1,Feather stacking headers 12+16 pin (hand-soldered)
J2,JST,S2B-PH-K-S(LF)(SN),3,1,PH 2-pin right-angle THT header (12V in)
J2 mate,JST,PHR-2,3,1,PH 2-pin housing
J2 mate,JST,SPH-002T-P0.5S,10,2,PH crimp contact 24-30AWG
J4 mate,JST,GHR-05V-S,3,1,GH 5-pin housing
J3 mate,JST,GHR-06V-S,3,1,GH 6-pin housing
J5 mate,JST,GHR-08V-S,3,1,GH 8-pin housing
J3-J5 mate,JST,SSHL-002T-P0.2,50,19,GH crimp contact 26-30AWG
